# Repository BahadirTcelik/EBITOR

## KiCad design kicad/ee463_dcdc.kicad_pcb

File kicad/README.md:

# KiCad project

Open `ee463_dcdc.kicad_pro` with KiCad 8, 9 or 10. Everything in this folder except the two Markdown plans is
generated from `netlist/schematic_netlist.py`, the single source of all components and connections.

| File | Content |
|---|---|
| `ee463_dcdc.kicad_sch` | schematic, one A3 sheet, 103 parts in five blocks. Connections are made with net labels; GND pins carry a GND symbol. Written in the KiCad 7 file format; newer versions convert it when saving |
| `ee463_dcdc.kicad_pro`, `ee463_dcdc.kicad_dru` | project file with the net classes and design rules of `layout_plan.md` section 4 (check them in Board Setup after the first save); custom rule for 0.5 mm around SW |
| `ee463_dcdc.kicad_pcb` | board, **placement only, not routed**: 100 × 70 mm, 4 layers, 103 footprints, draft pours, silkscreen. KiCad 7 file format plus the "do not populate" flag of the six DNP footprints, which needs KiCad 8 or newer (`out/ee463_dcdc_k7.kicad_pcb` is the same board without the flag) |
| `make_pcb.py` | board generator (pcbnew Python API): reads the schematic netlist, places the parts from its `PLACE` table, draws the draft pours and measures the placement distances. It refuses to overwrite a board that was changed after it wrote it (`--force` overrides) |
| `run_pcb_checks.bat` | KiCad DRC → `out\drc.rpt` and the course PCB-Checker (`..\PCB-Checker`, `--overload`) → `out\pcb_check.html` |
| `ee463.kicad_sym`, `sym-lib-table` | project symbol library: LTC3895 (31 leads + exposed pad, drawn in package order) |
| `ee463.pretty/`, `fp-lib-table` | project footprint library: LTC3895 FE38(31) with exposed pad and thermal vias; generic 2-position 5.00 mm terminal block |
| `make_kicad.py` | generator. Regenerating overwrites the schematic, so after editing the schematic by hand either stop regenerating or make the change in `netlist/schematic_netlist.py` |
| `run_kicad_checks.bat` | runs `kicad-cli`: ERC report, netlist, schematic PDF and a footprint-name check into `out/` |
| `ee463_dcdc_schematic_preview.pdf` | the schematic as plotted by kicad-cli 7.0.11 on 16 Nov 2026 (for reading without KiCad) |
| `compare_netlist.py` | compares `out/ee463_dcdc.net` with `netlist/pins.csv` |
| `footprints.md` | pin tables and footprints compared with the datasheets (16 Nov 2026) |
| `layout_plan.md` | floor plan as placed, measured distances, layer use, net classes and design rules, critical routes, check results, open points |
| `out/placement_checks.md`, `out/assembly_top.pdf`, `out/pcb_check_placement.html` | output of `make_pcb.py`; F.Fab drawing with all references; PCB-Checker report of the unrouted board (run without KiCad's DRC) |
| `pcb_checker.json` | PCB-Checker settings; keep it next to the project file |

## Status (17 Nov 2026)

- Schematic regenerated on 17 Nov (5 V rail of the current-limit circuit from the TL431, U5 and C32 removed, R30 added;
  assembly groups). Exported with `kicad-cli` 7.0.11: the netlist is identical to `netlist/pins.csv`
  (103 parts, 224 pads, 40 nets).
- **ERC of the new schematic has not been run** (KiCad 7's command line has no ERC): run `run_kicad_checks.bat` again.
  Result for the schematic of 16 Nov with KiCad 10.0.8: 0 errors, 6 warnings, all "symbol does not match the copy in the
  library" (Q1–Q3, U3, U4, RV1). The schematic holds copies of the KiCad 7 symbols; their pin numbers were checked
  against the datasheets. Do **not** run "Update Symbols from Library" without comparing the netlist again
  (`compare_netlist.py`). `+5V_CC` now carries a PWR_FLAG (it is fed through R29).
- Board placed by `make_pcb.py`, **not routed** (17 Nov). All placement distances of `layout_plan.md` section 2 are
  met; VIN pour 10.5 cm²; PCB-Checker on the unrouted board (without KiCad's DRC): 0 must fix, 2 should fix (4 layers;
  no test point on `VIN_IC`), 3 to check (thermal vias at Q1–Q3).
- KiCad 10.0.8 DRC of the board of 16 Nov: field `MPN` missing on the footprints, DNP flag missing, thermal reliefs at U1;
  all three are handled in `make_pcb.py` now (`layout_plan.md` section 7). The new board has not been checked with
  KiCad 10 yet (`run_pcb_checks.bat`).
- Do not press F8 for a first import: the footprints are already on the board. After a schematic change use
  `make_pcb.py` (before routing) or Tools → Update PCB from Schematic (after routing has started).
- Stack-up: 4 layers, 1.6 mm, 1 oz (sponsorship announcement: up to 200 × 200 mm, up to 4 layers); L2 is one GND zone.
  Check the layer thicknesses in Board Setup → Physical Stackup before ordering.
- Fabrication outputs (Gerber + drill) go to `fab/`; run PCB-Checker on the final submission zip.

## Regenerating

```
pip install sexpdata
set KICAD_SYMBOL_DIR=C:\Program Files\KiCad\10.0\share\kicad\symbols
python make_kicad.py
```

Board (Linux or the KiCad command prompt; needs `pcbnew` and `kicad-cli` 7 or newer):

```
python make_pcb.py
```

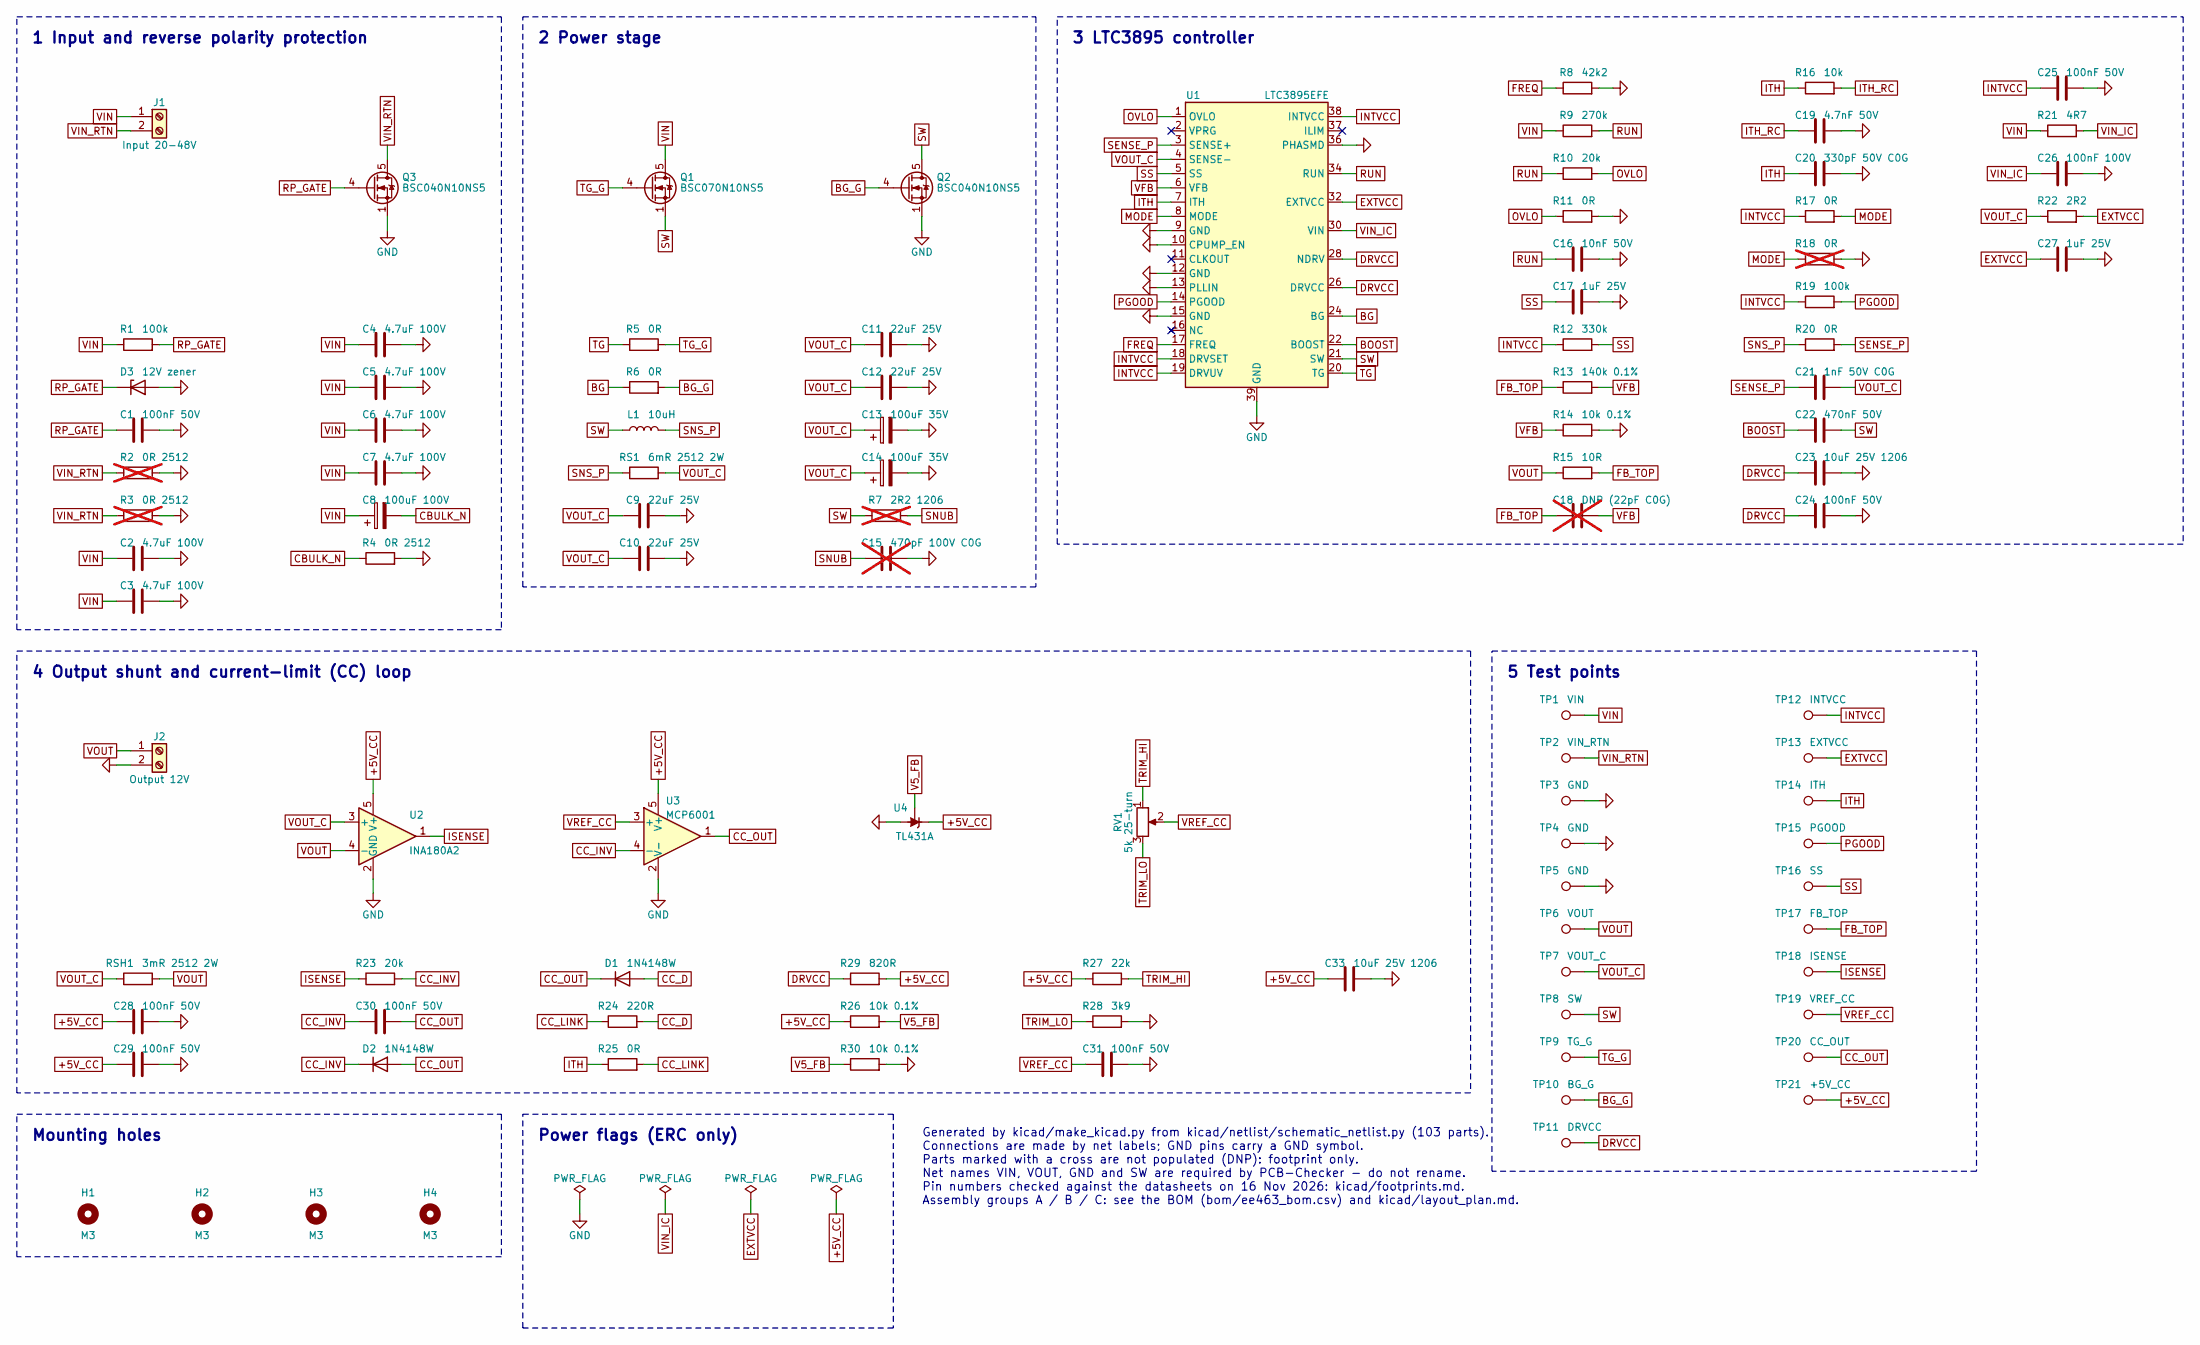
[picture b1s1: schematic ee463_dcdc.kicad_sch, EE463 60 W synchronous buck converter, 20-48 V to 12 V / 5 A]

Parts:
C1, C24, C25, C28, C29, C30, C31: 100nF 50V; C_0805_2012Metric; MPN CL21B104KBCNNNC
C2, C3, C4, C5, C6, C7: 4.7uF 100V; C_1210_3225Metric; MPN CL32B475KCVZW6E
C8: 100uF 100V; CP_Radial_D12.5mm_P5.00mm; MPN EEU-FC2A101
C9, C10, C11, C12: 22uF 25V; C_1210_3225Metric; MPN GRM32ER71E226ME15L
C13, C14: 100uF 35V; CP_Elec_8x6.7; MPN A768KE107M1VLAE036
C15: 470pF 100V C0G; C_0805_2012Metric; not fitted
C16: 10nF 50V; C_0805_2012Metric; MPN CL21B103KBANNNC
C17, C27: 1uF 25V; C_0805_2012Metric; MPN C2012X7R1E105K125AB
C18: DNP (22pF C0G); C_0805_2012Metric; not fitted
C19: 4.7nF 50V; C_0805_2012Metric; MPN CL21B472KBANNNC
C20: 330pF 50V C0G; C_0805_2012Metric
C21: 1nF 50V C0G; C_0805_2012Metric
C22: 470nF 50V; C_0805_2012Metric; MPN GRM21BR71H474KA88L
C23, C33: 10uF 25V 1206; C_1206_3216Metric; MPN GRM31CR71E106KA12L
C26: 100nF 100V; C_0805_2012Metric
D1, D2: 1N4148W; D_SOD-123; MPN 1N4148W
D3: 12V zener; D_SOD-123; MPN BZT52C12-HE3-08
H1, H2, H3, H4: M3; MountingHole_3.2mm_M3
J1: Input 20-48V; TerminalBlock_Generic_1x02_P5.00mm_Drill1.5mm
J2: Output 12V; TerminalBlock_Generic_1x02_P5.00mm_Drill1.5mm
L1: 10uH; L_Wuerth_HCI-1890; MPN 74435561100
Q1: BSC070N10NS5; TDSON-8-1; MPN BSC070N10NS5ATMA1
Q2, Q3: BSC040N10NS5; TDSON-8-1; MPN BSC040N10NS5ATMA1
R1, R19: 100k; R_0805_2012Metric; MPN RC0805FR-07100KL
R2, R3: 0R 2512; R_2512_6332Metric; MPN RC2512JK-070RL; not fitted
R4: 0R 2512; R_2512_6332Metric; MPN RC2512JK-070RL
R5, R6, R11, R17, R20, R25: 0R; R_0805_2012Metric; MPN RC0805JR-070RL
R7: 2R2 1206; R_1206_3216Metric; not fitted
R8: 42k2; R_0805_2012Metric; MPN RC0805FR-0742K2L
R9: 270k; R_0805_2012Metric
R10, R23: 20k; R_0805_2012Metric
R12: 330k; R_0805_2012Metric; MPN RC0805FR-07330KL
R13: 140k 0.1%; R_0805_2012Metric; MPN RT0805BRD07140KL
R14, R26, R30: 10k 0.1%; R_0805_2012Metric; MPN RT0805BRD0710KL
R15: 10R; R_0805_2012Metric; MPN RC0805FR-0710RL
R16: 10k; R_0805_2012Metric; MPN RC0805FR-0710KL
R18: 0R; R_0805_2012Metric; not fitted
R21: 4R7; R_0805_2012Metric
R22: 2R2; R_0805_2012Metric
R24: 220R; R_0805_2012Metric; MPN RC0805FR-07220RL
R27: 22k; R_0805_2012Metric
R28: 3k9; R_0805_2012Metric
R29: 820R; R_0805_2012Metric
RS1: 6mR 2512 2W; R_2512_6332Metric; MPN PA2512FKF7W0R006E
RSH1: 3mR 2512 2W; R_2512_6332Metric; MPN PA2512FKF7W0R003E
RV1: 5k 25-turn; Potentiometer_Bourns_3296W_Vertical; MPN 3296W-1-502LF
TP1: VIN; TestPoint_Loop_D2.50mm_Drill1.0mm
TP2: VIN_RTN; TestPoint_Loop_D2.50mm_Drill1.0mm
TP3, TP4, TP5: GND; TestPoint_Loop_D2.50mm_Drill1.0mm
TP6: VOUT; TestPoint_Loop_D2.50mm_Drill1.0mm
TP7: VOUT_C; TestPoint_Loop_D2.50mm_Drill1.0mm
TP8: SW; TestPoint_Loop_D2.50mm_Drill1.0mm
TP9: TG_G; TestPoint_Loop_D2.50mm_Drill1.0mm
TP10: BG_G; TestPoint_Loop_D2.50mm_Drill1.0mm
TP11: DRVCC; TestPoint_Loop_D2.50mm_Drill1.0mm
TP12: INTVCC; TestPoint_Loop_D2.50mm_Drill1.0mm
TP13: EXTVCC; TestPoint_Loop_D2.50mm_Drill1.0mm
TP14: ITH; TestPoint_Loop_D2.50mm_Drill1.0mm
TP15: PGOOD; TestPoint_Loop_D2.50mm_Drill1.0mm
TP16: SS; TestPoint_Loop_D2.50mm_Drill1.0mm
TP17: FB_TOP; TestPoint_Loop_D2.50mm_Drill1.0mm
TP18: ISENSE; TestPoint_Loop_D2.50mm_Drill1.0mm
TP19: VREF_CC; TestPoint_Loop_D2.50mm_Drill1.0mm
TP20: CC_OUT; TestPoint_Loop_D2.50mm_Drill1.0mm
TP21: +5V_CC; TestPoint_Loop_D2.50mm_Drill1.0mm
U1: LTC3895EFE; LTC3895_TSSOP-38-31-1EP_4.4x9.7mm_P0.5mm_EP2.74x4.75mm_Ther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; MPN LTC3895EFE#TRPBF
U2: INA180A2; SOT-23-5; MPN INA180A2IDBVR
U3: MCP6001; SOT-23-5; MPN MCP6001T-E/OT
U4: TL431A; SOT-23; MPN TL431AIDBZR

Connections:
+5V_CC: C28.1, C29.1, C33.1, R26.1, R27.1, R29.2, TP21.1, U2.5 (V+), U3.5 (V+), U4.1 (K)
BG: R6.1, U1.24 (BG)
BG_G: Q2.4 (G), R6.2, TP10.1
BOOST: C22.1, U1.22 (BOOST)
CBULK_N: C8.2, R4.1
CC_D: D1.2 (A), R24.2
CC_INV: C30.1, D2.1 (K), R23.2, U3.4 (-)
CC_LINK: R24.1, R25.2
CC_OUT: C30.2, D1.1 (K), D2.2 (A), TP20.1, U3.1
DRVCC: C23.1, C24.1, R29.1, TP11.1, U1.26 (DRVCC), U1.28 (NDRV)
EXTVCC: C27.1, R22.2, TP13.1, U1.32 (EXTVCC)
FB_TOP: C18.1, R13.1, R15.2, TP17.1
FREQ: R8.1, U1.17 (FREQ)
GND: C1.2, C2.2, C3.2, C4.2, C5.2, C6.2, C7.2, C9.2, C10.2, C11.2, C12.2, C13.2, C14.2, C15.2, C16.2, C17.2, C19.2, C20.2, C23.2, C24.2, C25.2, C26.2, C27.2, C28.2, C29.2, C31.2, C33.2, D3.2 (A), J2.2, Q2.1 (S), Q2.2 (S), Q2.3 (S), Q3.1 (S), Q3.2 (S), Q3.3 (S), R2.2, R3.2, R4.2, R8.2, R11.2, R14.2, R18.2, R28.2, R30.2, TP3.1, TP4.1, TP5.1, U1.9 (GND), U1.10 (CPUMP_EN), U1.12 (GND), U1.13 (PLLIN), U1.15 (GND), U1.36 (PHASMD), U1.39 (GND), U2.2 (GND), U3.2 (V-), U4.3 (A)
INTVCC: C25.1, R12.1, R17.1, R19.1, TP12.1, U1.18 (DRVSET), U1.19 (DRVUV), U1.38 (INTVCC)
ISENSE: R23.1, TP18.1, U2.1
ITH: C20.1, R16.1, R25.1, TP14.1, U1.7 (ITH)
ITH_RC: C19.1, R16.2
MODE: R17.2, R18.1, U1.8 (MODE)
OVLO: R10.2, R11.1, U1.1 (OVLO)
PGOOD: R19.2, TP15.1, U1.14 (PGOOD)
RP_GATE: C1.1, D3.1 (K), Q3.4 (G), R1.2
RUN: C16.1, R9.2, R10.1, U1.34 (RUN)
SENSE_P: C21.1, R20.2, U1.3 (SENSE+)
SNS_P: L1.2, R20.1, RS1.1
SNUB: C15.1, R7.2
SS: C17.1, R12.2, TP16.1, U1.5 (SS)
SW: C22.2, L1.1, Q1.1 (S), Q1.2 (S), Q1.3 (S), Q2.5 (D), R7.1, TP8.1, U1.21 (SW)
TG: R5.1, U1.20 (TG)
TG_G: Q1.4 (G), R5.2, TP9.1
TRIM_HI: R27.2, RV1.1
TRIM_LO: R28.1, RV1.3
V5_FB: R26.2, R30.1, U4.2 (REF)
VFB: C18.2, R13.2, R14.1, U1.6 (VFB)
VIN: C2.1, C3.1, C4.1, C5.1, C6.1, C7.1, C8.1, J1.1, Q1.5 (D), R1.1, R9.1, R21.1, TP1.1
VIN_IC: C26.1, R21.2, U1.30 (VIN)
VIN_RTN: J1.2, Q3.5 (D), R2.1, R3.1, TP2.1
VOUT: J2.1, R15.1, RSH1.2, TP6.1, U2.4 (-)
VOUT_C: C9.1, C10.1, C11.1, C12.1, C13.1, C14.1, C21.2, R22.1, RS1.2, RSH1.1, TP7.1, U1.4 (SENSE-), U2.3 (+)
VREF_CC: C31.1, RV1.2, TP19.1, U3.3 (+)

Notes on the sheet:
1 Input and reverse polarity protection
2 Power stage
3 LTC3895 controller
4 Output shunt and current-limit (CC) loop
5 Test points
Mounting holes
Power flags (ERC only)
Generated by kicad/make_kicad.py from kicad/netlist/schematic_netlist.py (103 parts). Connections are made by net labels; GND pins carry a GND symbol. Parts marked with a cross are not populated (DNP): footprint only. Net names VIN, VOUT, GND and SW are required by PCB-Checker - do not rename. Pin 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

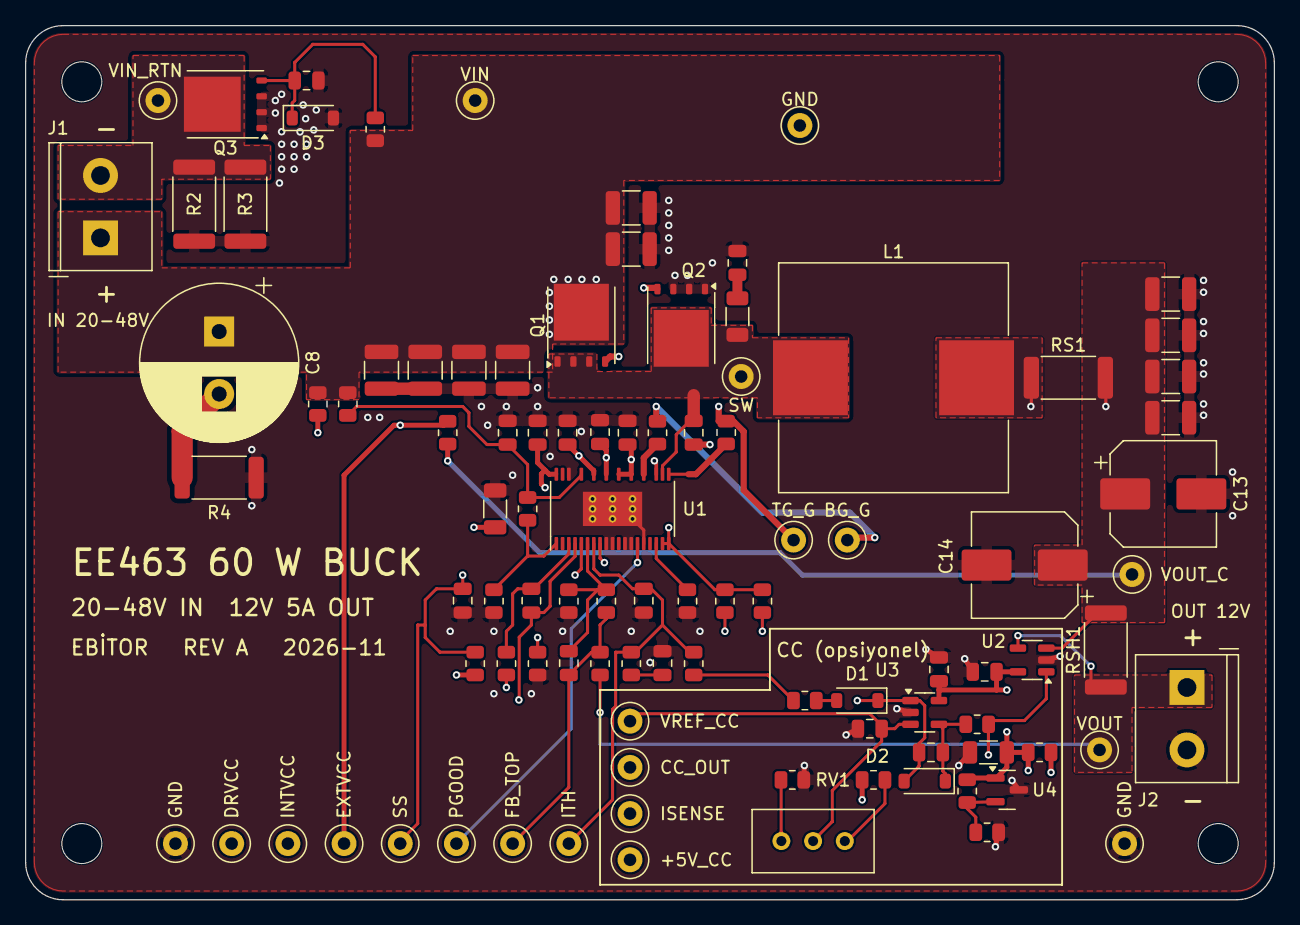
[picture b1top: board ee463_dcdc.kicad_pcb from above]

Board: 4 copper layers, 100.0 x 70.0 mm, 103 parts (0 on the bottom side), 40 nets.

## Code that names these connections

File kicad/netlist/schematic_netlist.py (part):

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add("C8", "100uF 100V", "Aluminium electrolytic 100 uF 100 V, radial 12.5x20 mm, lead spacing 5 mm", {"+": "VIN", "-": "CBULK_N"}, B, "EEU-FC2A101", EK, OVS,
    "110.06", "Capacitor_THT:CP_Radial_D12.5mm_P5.00mm",
    note="can is 12.5 mm (distributor data), not 10 mm; 0.18 ohm impedance and 0.67 A ripple at 100 kHz (distributor data): confirm in the Panasonic datasheet")
r("R4", "0R 2512", "CBULK_N", "GND", B, "RC2512JK-070RL", OVS, "17.38", fp=R2512, sup=EK, desc="0 ohm jumper 2512 (damping resistor position)",
  note="replace by 0.22-0.33 ohm if the bulk capacitor ESR is below 0.2 ohm")

# ---------------------------------------------------------------- 2 power stage
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r("R6", "0R", "BG", "BG_G", B, "RC0805JR-070RL", OVS, "7.24", sup=EK, desc="0 ohm link 0805 (gate resistors, option links)")
add("L1", "10uH", "Power inductor WE-HCI 1890, Isat 10 A (-10 %) / 21.5 A (-30 %), DCR 6.9 mOhm +-8 %", {"1": "SW", "2": "SNS_P"}, B, "74435561100", EK, OWN, "447.12",
    "Inductor_SMD:L_Wuerth_HCI-1890", note="no tracks underneath, only GND pour")
r("RS1", "6mR 2512 2W", "SNS_P", "VOUT_C", B, "PA2512FKF7W0R006E", OVS, "67.77", fp=R2512, sup=EK, desc="Current sense resistor 6 mOhm 1 % 2 W",
  note="Kelvin connections to U1 pins 3 and 4")
for i in range(4):
    c(f"C{9+i}", "22uF 25V", "VOUT_C", "GND", B, "GRM32ER71E226ME15L", OWN, "58.89", fp=C1210, sup=EK, desc="Ceramic 22 uF 25 V X7R 1210",
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r("R16", "10k", "ITH", "ITH_RC", B, "RC0805FR-0710KL", OVS, "7.24", sup=EK, note="Rc, design A (design B: 4.7k)")
c("C19", "4.7nF 50V", "ITH_RC", "GND", B, "CL21B472KBANNNC", OVS, "7.57", sup=EK, note="Cc, design A (design B: 22 nF)")
c("C20", "330pF 50V C0G", "ITH", "GND", B, note="Cp")
r("R17", "0R", "INTVCC", "MODE", B, "RC0805JR-070RL", OVS, "7.24", sup=EK, note="forced continuous; 100k here = pulse-skipping")
r("R18", "0R", "MODE", "GND", B, fit=False, note="DNP: Burst Mode (remove R17)")
r("R19", "100k", "INTVCC", "PGOOD", B, "RC0805FR-07100KL", OVS, "7.24", sup=EK)
r("R20", "0R", "SNS_P", "SENSE_P", B, "RC0805JR-070RL", OVS, "7.24", sup=EK, note="sense filter position (up to 100 ohm); nothing in the SENSE- line")
c("C21", "1nF 50V C0G", "SENSE_P", "VOUT_C", B, note="at U1 pins 3-4")
c("C22", "470nF 50V", "BOOST", "SW", B, "GRM21BR71H474KA88L", OVS, "16.65", sup=EK, note="within 5 mm of pins 21-22, same side, no vias")
c("C23", "10uF 25V 1206", "DRVCC", "GND", B, "GRM31CR71E106KA12L", "not in stock at e-komponent on 16 Nov -> Ozdisan", "23.89",
  fp="Capacitor_SMD:C_1206_3216Metric", desc="Ceramic 10 uF 25 V X7R 1206", note="at pin 26")
c("C24", "100nF 50V", "DRVCC", "GND", B, "CL21B104KBCNNNC", OVS, "7.24", sup=EK)
c("C25", "100nF 50V", "INTVCC", "GND", B, "CL21B104KBCNNNC", OVS, "7.24", sup=EK, note="at pin 38")
r("R21", "4R7", "VIN", "VIN_IC", B)
c("C26", "100nF 100V", "VIN_IC", "GND", B, desc="Ceramic 100 nF 100 V X7R 0805", note="at pin 30")
r("R22", "2R2", "VOUT_C", "EXTVCC", B)
c("C27", "1uF 25V", "EXTVCC", "GND", B, "C2012X7R1E105K125AB", OVS, "16.65", sup=EK, note="at pin 32")

# ---------------------------------------------------------------- 4 output and current limit loop
B = "4 Output shunt and current-limit (CC) loop"
r("RSH1", "3mR 2512 2W", "VOUT_C", "VOUT", B, "PA2512FKF7W0R003E", OVS, "72.01", fp=R2512, sup=EK, desc="Shunt 3 mOhm 1 % 2 W", note="Kelvin to U2")
add("J2", "Output 12V", TBD, {"1": "VOUT", "2": "GND"}, B, "", OZ, GEN, "",
    TB, note=TBN + "; 7.75 A in current limit, 10 A for 3 ms")
add("U2", "INA180A2", "Current-sense amplifier, gain 50, SOT-23-5", {"1 OUT": "ISENSE", "2 GND": "GND", "3 IN+": "VOUT_C", "4 IN-": "VOUT",
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print("Assembly groups: " + ", ".join(f"{g} {count[g]} parts ({sum(1 for x in C if x['grp'] == g and x['fit'])} fitted, "
                                      f"{total_grp[g]:.0f} TRY priced)" for g in "ABC"))
open_b = check_without({"B"})
print("Group B not fitted: " + ("every remaining net has at least two fitted pins (ITH: "
      + ", ".join(p for p in sorted(r_ + "." + q.split()[0] for r_, q, f_ in nets["ITH"] if not r_.startswith("TP")
                                    and next(x for x in C if x["ref"] == r_)["grp"] != "B")) + "; VFB: "
      + ", ".join(sorted(r_ + "." + q.split()[0] + ("" if f_ else " (DNP)") for r_, q, f_ in nets["VFB"])) + ")"
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
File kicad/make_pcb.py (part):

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    "C17": (37.8, B, 270), "R11": (40.2, B, 270), "C21": (42.6, B, 270), "R14": (45.0, B, 270), "R13": (47.4, B, 90),
    "C20": (49.8, B, 270), "R8": (52.2, B, 270), "R19": (54.6, B, 270), "R17": (57.0, B, 270),
    "R12": (37.8, C_, 90), "R20": (40.2, C_, 90), "R18": (42.6, C_, 270), "C18": (45.0, C_, 90), "R15": (47.4, C_, 90),
    "R16": (49.8, C_, 270), "C19": (52.2, C_, 90), "R25": (54.6, C_, 270),      # R25: CC link, stays at the ITH pin
    # assembly group B: current-limit (CC) circuit, one block beside the shunt at the lower board edge (frame CC_FRAME).
    # Signal flow right to left: RSH1 -> U2 -> R23 -> U3 (integrator C30, clamp D2) -> D1 -> R24 -> CC_LINK -> R25 at U1.
    "U2": (80.6, 50.8, 180), "C28": (76.8, 51.75, 180), "C29": (73.14, 51.55, 90),
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    ("GND", "F.Cu", 0, 0.3, False, "board"),
    ("GND", "In1.Cu", 0, 0.3, False, "board"),          # L2: unbroken ground plane
    ("GND", "B.Cu", 0, 0.3, False, "board"),
    # second copper on L4: so far connected only through the VIN and VOUT_C test point pins; the stitching
    # vias next to Q1 and the output capacitors are placed in the routing step
    ("VIN", "B.Cu", 2, 0.5, True, [(26, 2.4), (VIN_X1, 2.4), (VIN_X1, 12.4), (47.9, 12.4), (47.9, 25.5), (26, 25.5)]),
    ("VOUT_C", "B.Cu", 2, 0.3, True, [(84.6, 19.0), (91.2, 19.0), (91.2, 47.8), (84.6, 47.8)]),
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        add(f"{cap} GND pad to Q2 source pads (edge)", edge(cap, dict(netname="GND"), "Q2", dict(pins=["1", "2", "3"])), 5)
    add("U1 TG pin 20 to Q1 gate pad (centres)", centre("U1", "20", "Q1", "4"), 15)
    add("U1 BG pin 24 to Q2 gate pad (centres)", centre("U1", "24", "Q2", "4"), 15)
    add("C22 to U1 BOOST pin 22 (edge)", edge("C22", dict(netname="BOOST"), "U1", dict(pins=["22"])), 5)
    add("C22 to U1 SW pin 21 (edge)", edge("C22", dict(netname="SW"), "U1", dict(pins=["21"])), 5)
    add("R13 to U1 VFB pin 6 (edge)", edge("R13", dict(netname="VFB"), "U1", dict(pins=["6"])), 10)
    add("R14 to U1 VFB pin 6 (edge)", edge("R14", dict(netname="VFB"), "U1", dict(pins=["6"])), 10)
    for cap, netname, ic, pin in (("C24", "DRVCC", "U1", "26"), ("C25", "INTVCC", "U1", "38"), ("C26", "VIN_IC", "U1", "30"),
                                  ("C27", "EXTVCC", "U1", "32"), ("C28", "+5V_CC", "U2", "5"), ("C29", "+5V_CC", "U3", "5"),
                                  ("C31", "VREF_CC", "U3", "3"), ("C33", "+5V_CC", "U4", "1")):
        add(f"{cap} to {ic} pin {pin} {netname} (edge)", edge(cap, dict(netname=netname), ic, dict(pins=[pin])), 4)
    add("C23 (10 uF) to U1 DRVCC pin 26 (edge)", edge("C23", dict(netname="DRVCC"), "U1", dict(pins=["26"])), 30)

    # courtyards: no overlap, nothing inside the board edge keep-out, nothing under L1
    cy = {}
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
